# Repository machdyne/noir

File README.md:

# Noir Computer

Noir is an FPGA computer designed by Lone Dynamics Corporation.

This repo contains schematics, PCB layouts, pinouts, a 3D-printable case, example gateware and documentation.

Find more information on the [Noir product page](https://machdyne.com/product/noir-computer/).

## Dual-Core Bitstream

There is now a dual-core bitstream optimized for speed that significantly decreases boot time and adds a second RISC-V core.

In addition to updating to this bitstream (`images/v0/noir_dual.bit`), make sure you copy the `images/linux/noir_dual.dtb` file to the SD card and update `boot.json` to use `noir_dual.dtb`.

## Programming Noir

Noir has a JTAG interface and ships with a [DFU bootloader](https://github.com/machdyne/tinydfu-bootloader) that allows the included flash [MMOD](https://machdyne.com/product/mmod) to be programmed over the USB-C port.

### DFU

The DFU bootloader is available for 5 seconds after power-on, issuing a DFU command during this period will stop the boot process until the DFU device is detached. If no command is received the boot process will continue and the user gateware will be loaded.

Install [dfu-util](http://dfu-util.sourceforge.net) (Debian/Ubuntu):

```
$ sudo apt install dfu-util
```

Update the user gateware on the flash MMOD:

```
$ sudo dfu-util -a 0 -D image.bit
```

Detach the DFU device and continue the boot process:

```
$ sudo dfu-util -a 0 -e
```

It is possible to update the bootloader itself using DFU but you shouldn't attempt this unless you have a JTAG programmer (or another method to program the MMOD) available, in case you need to restore the bootloader.

### JTAG

These examples assume you're using a "USB Blaster" JTAG cable, see the header pinout below. You will need to have [openFPGALoader](https://github.com/trabucayre/openFPGALoader) installed.

Program the configuration SRAM:

```
openFPGALoader -c usb-blaster image.bit
```

Program the flash MMOD:

```
openFPGALoader -f -c usb-blaster images/bootloader/tinydfu_noir.bit
```

## Blinky 

Building the blinky example requires [Yosys](https://github.com/YosysHQ/yosys), [nextpnr-ecp5](https://github.com/YosysHQ/nextpnr) and [Project Trellis](https://github.com/YosysHQ/prjtrellis).

Assuming they are installed, you can simply type `make` to build the gateware, which will be written to output/blinky.bin. You can then use [openFPGALoader](https://github.com/trabucayre/openFPGALoader) or dfu-util to write the gateware to the device.

## Linux

See the [Kakao Linux](https://github.com/machdyne/kakao) repo for the latest instructions.

### Prebuilt Images

Copy the files from the `images/linux` directory to the root directory of a FAT-formatted MicroSD card.

Noir ships with LiteX gateware on the user gateware section of the MMOD that is compatible with these images. After several seconds the Linux penguin should appear on the screen (HDMI) followed by a login prompt.

### Building Linux

Please follow the setup instructions in the [linux-on-litex-vexriscv](https://github.com/litex-hub/linux-on-litex-vexriscv) repo and then:

1. Build the Linux-capable gateware:

```
$ cd linux-on-litex-vexriscv
$ ./make.py --board noir --uart-baudrate 115200 --build

$ ls build/noir
```

2. Write the gateware to the MMOD using USB DFU:

```
$ sudo dfu-util -a 0 -D build/noir/gateware/noir.bit
```

3. Copy the device tree binary `build/noir/noir.dtb` to a FAT-formatted MicroSD card.

4. Build the Linux kernel and root filesystem:

```
$ cd ..
$ git clone http://github.com/buildroot/buildroot
$ cd buildroot
$ make BR2_EXTERNAL=../linux-on-litex-vexriscv/buildroot/ litex_vexriscv_usbhost_defconfig
```

Optionally customize the kernel and buildroot packages:

```
$ make menuconfig
```

Build the kernel and rootfs:

```
$ make
$ ls output/images
```

5. Copy the `Image` and `rootfs.cpio` files from output/images to the MicroSD card.

6. Copy the OpenSBI binary (included in this repo as `noir/images/linux/opensbi.bin`) to the MicroSD card. Alternatively, you can build this binary by following [these instructions](https://github.com/litex-hub/linux-on-litex-vexriscv#-generating-the-opensbi-binary-optional).

7. Copy `noir/images/linux/boot.json` to the MicroSD card.

8. Power-cycle Noir. After Linux has finished booting you should see a login prompt on the HDMI display.

## LiteX

### Installing LiteX

If you haven't yet installed LiteX please see the [LiteX quick start guide](https://github.com/enjoy-digital/litex#quick-start-guide) for details on installing LiteX.

### Building Custom Gateware

Build the LiteX gateware:

```
$ cd litex-boards/litex_boards/targets
$ ./machdyne_noir.py --cpu-type=vexriscv --cpu-variant=lite --sys-clk-freq 40000000 --uart-baudrate 1000000 --uart-name serial --build
```

Program the LiteX gateware to SRAM over JTAG:

```
$ ./machdyne_noir.py --cable usb-blaster --load
```

Or program the LiteX gateware to flash over DFU:

```
$ sudo dfu-util -a 0 -D build/machdyne_noir/gateware/machdyne_noir.bit
```

## JTAG Header

The 3.3V JTAG header can be used to program the FPGA SRAM as well as the MMOD flash memory. It can also be used to provide power (5V) to the board.

```
1 2
3 4
5 6
```

| Pin | Signal |
| --- | ------ |
| 1 | TCK |
| 2 | TDI |
| 3 | TDO |
| 4 | TMS |
| 5 | 5V0 |
| 6 | GND |

## Resources

 * [fpga-dac audio player](https://github.com/machdyne/fpga-dac)

## Board Revisions

| Revision | Notes |
| -------- | ----- |
| V0 | Initial version |
| V1 | Work in progress; adds composite video DAC output to 3.5mm jack |

## License

The contents of this repo are released under the [Lone Dynamics Open License](LICENSE.md) with the following exceptions:

- The KiCad design files contain parts of the [kicad-pmod](https://github.com/mithro/kicad-pmod) library which is released under the [Apache License, Version 2.0](https://www.apache.org/licenses/LICENSE-2.0.html).

- The KiCad design files may contain symbols and footprints released under other licenses; please contact us if we've failed to give proper attribution.

Note: You can use these designs for commercial purposes but we ask that instead of producing exact clones, that you either replace our trademarks and logos with your own or add your own next to ours.

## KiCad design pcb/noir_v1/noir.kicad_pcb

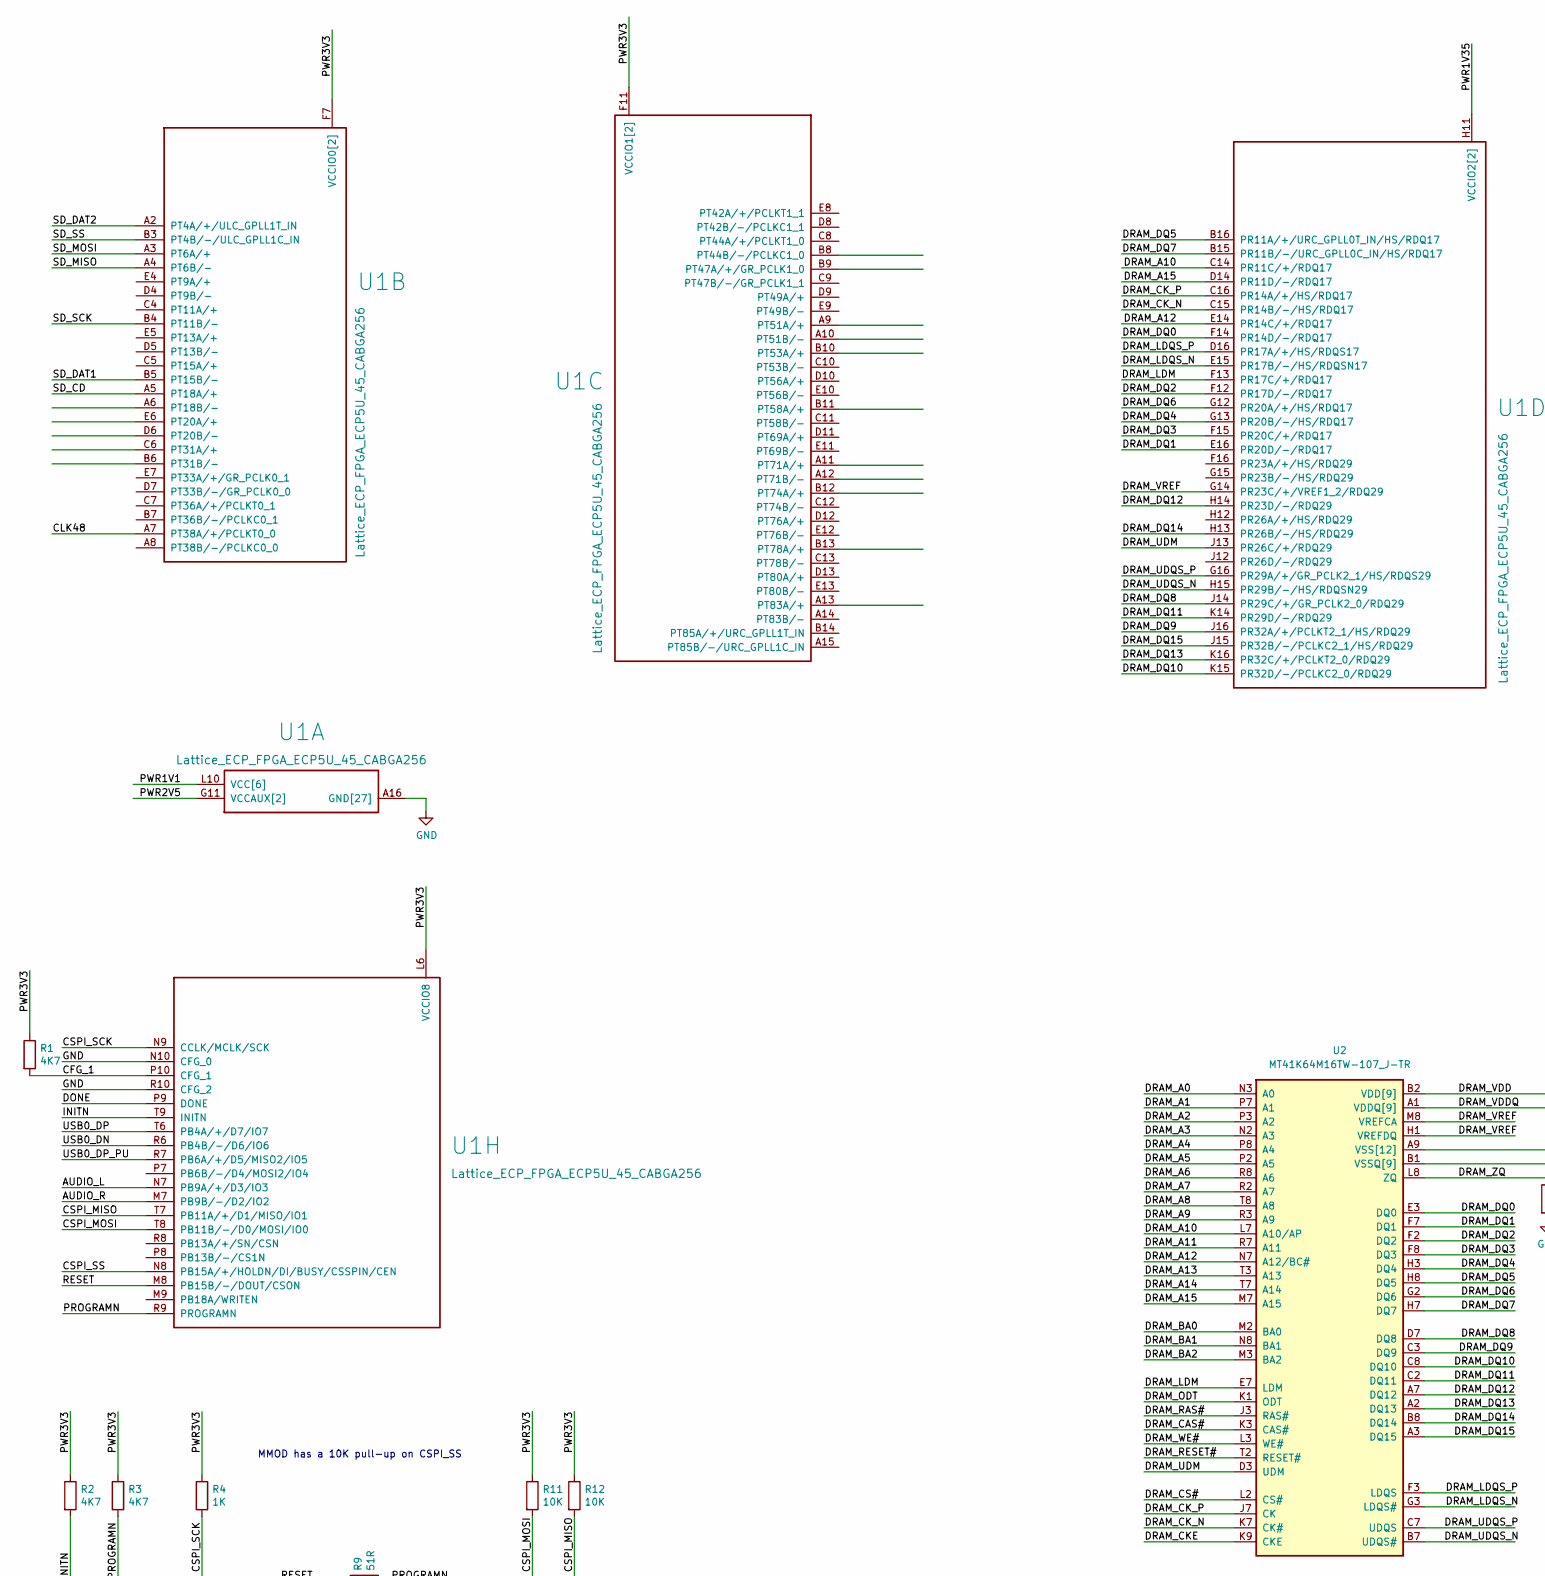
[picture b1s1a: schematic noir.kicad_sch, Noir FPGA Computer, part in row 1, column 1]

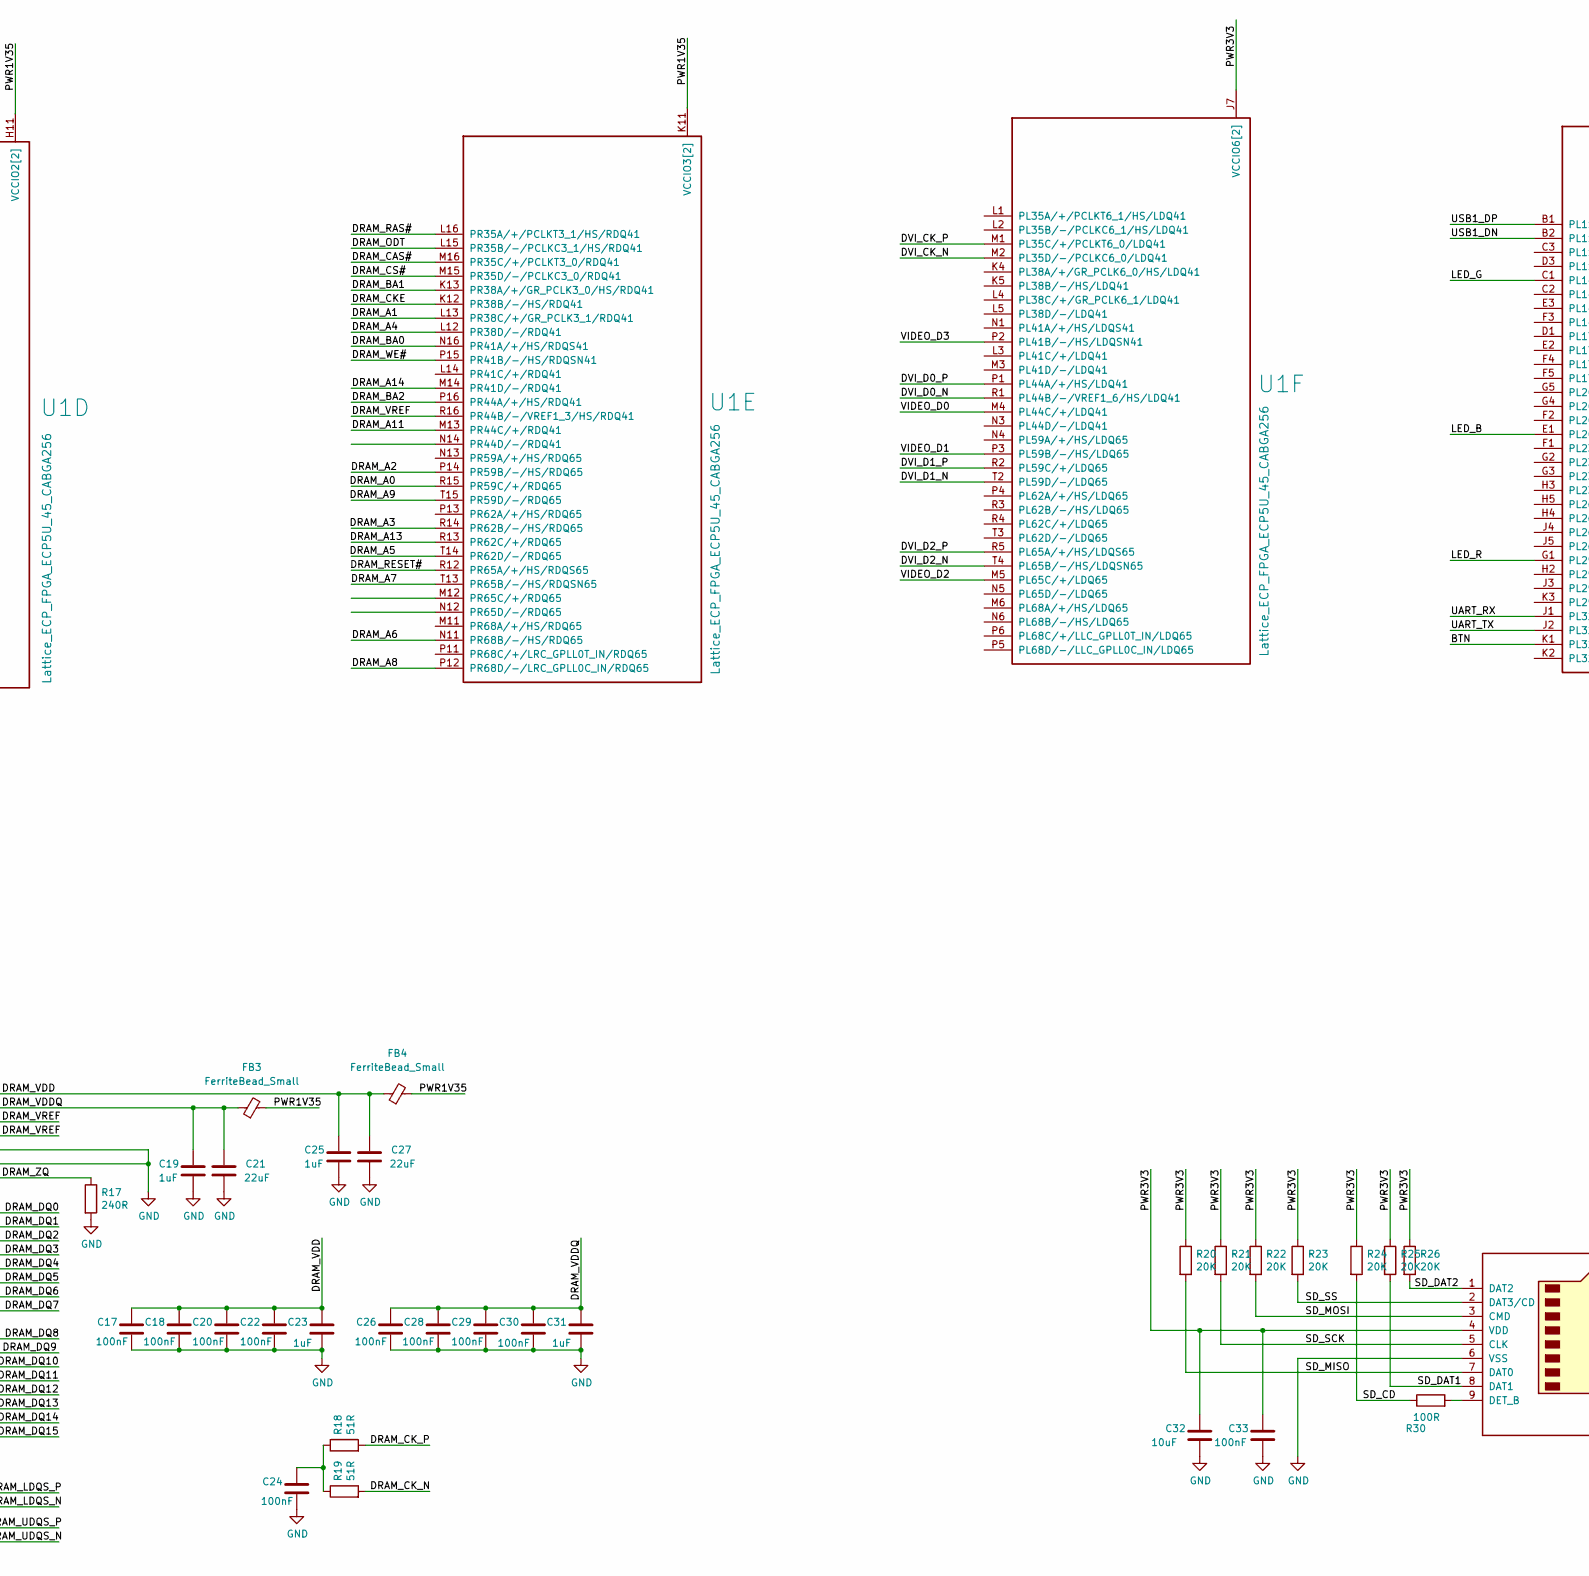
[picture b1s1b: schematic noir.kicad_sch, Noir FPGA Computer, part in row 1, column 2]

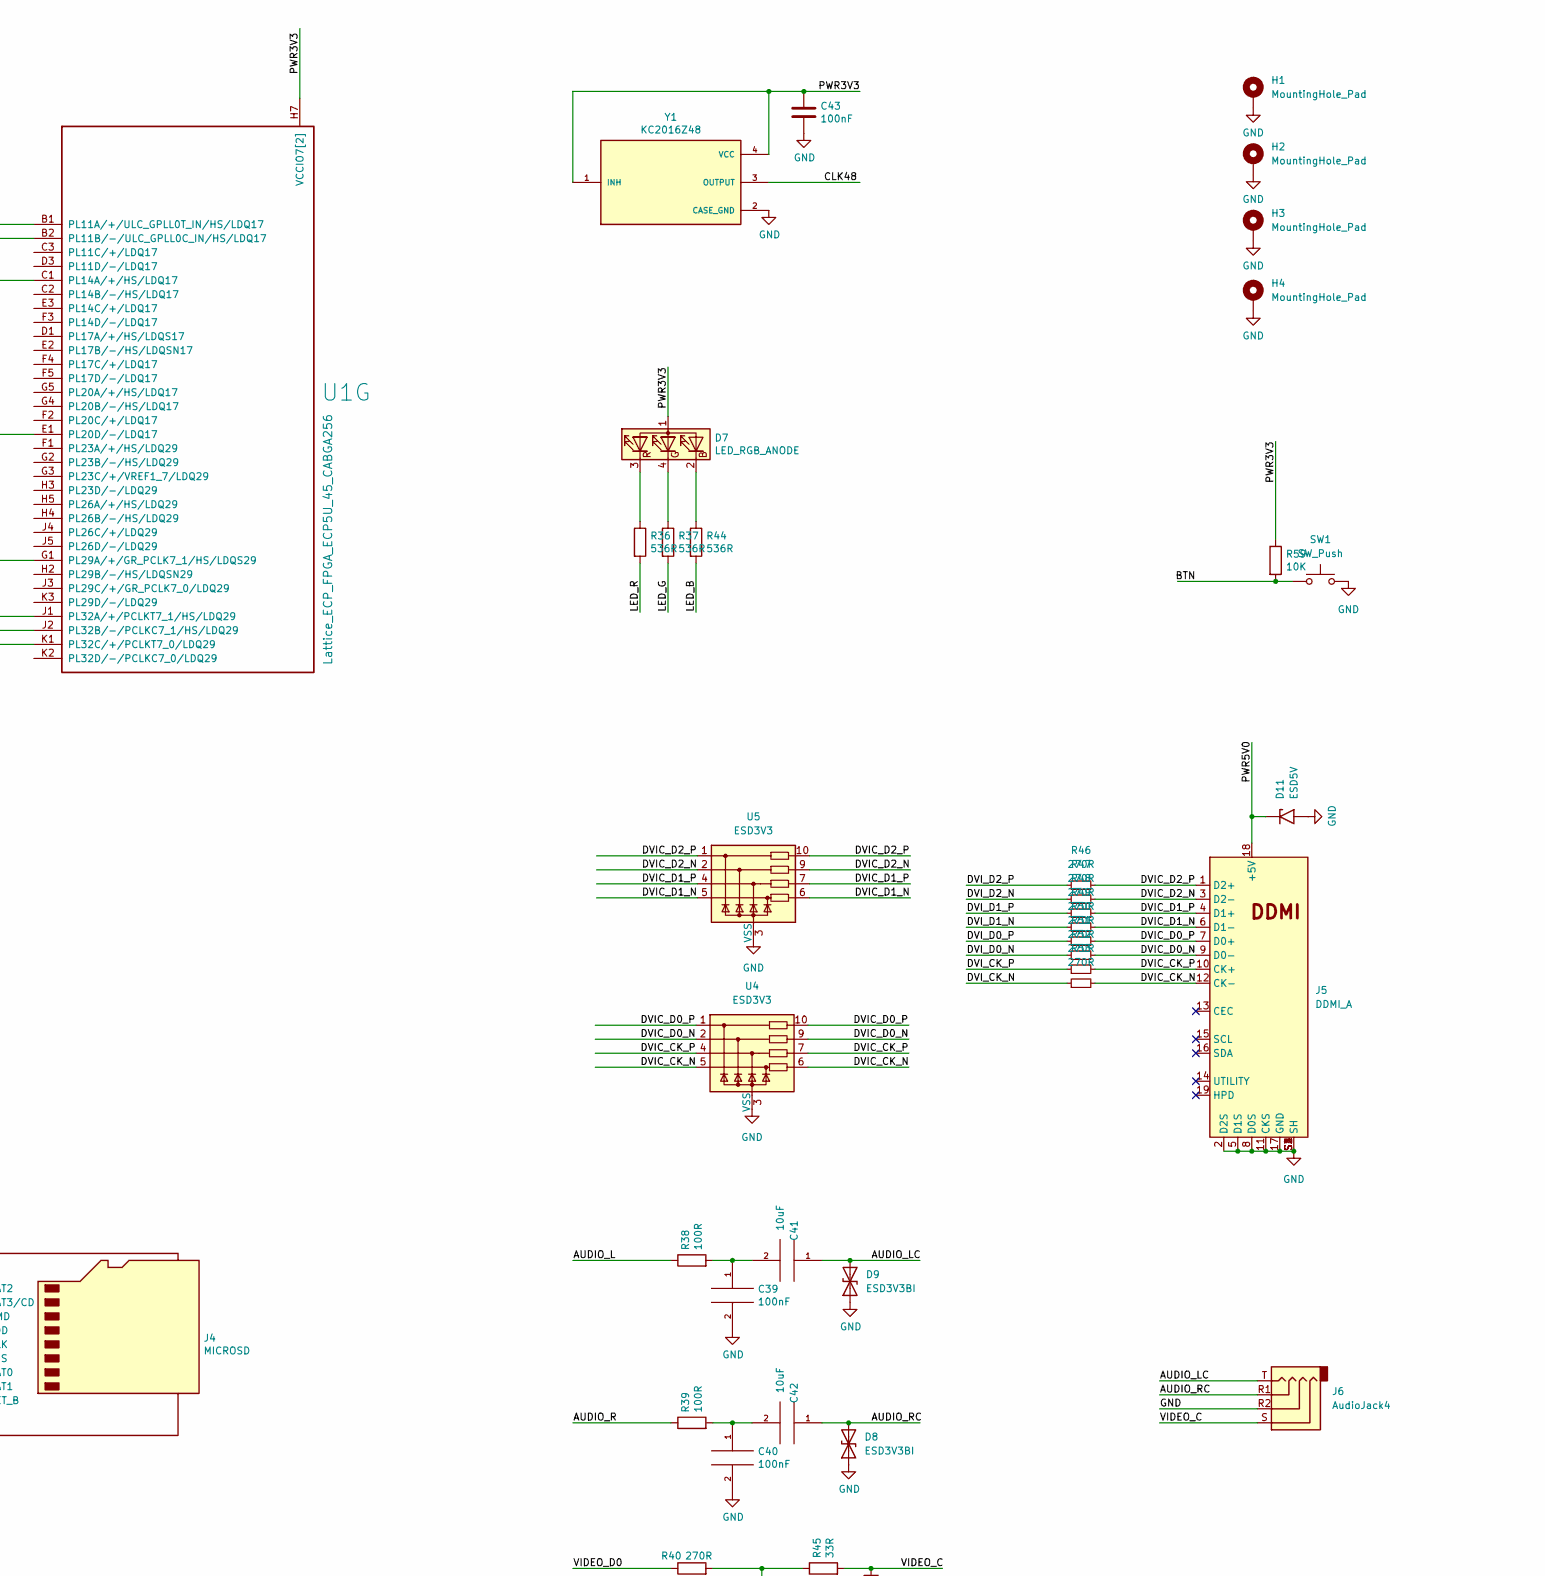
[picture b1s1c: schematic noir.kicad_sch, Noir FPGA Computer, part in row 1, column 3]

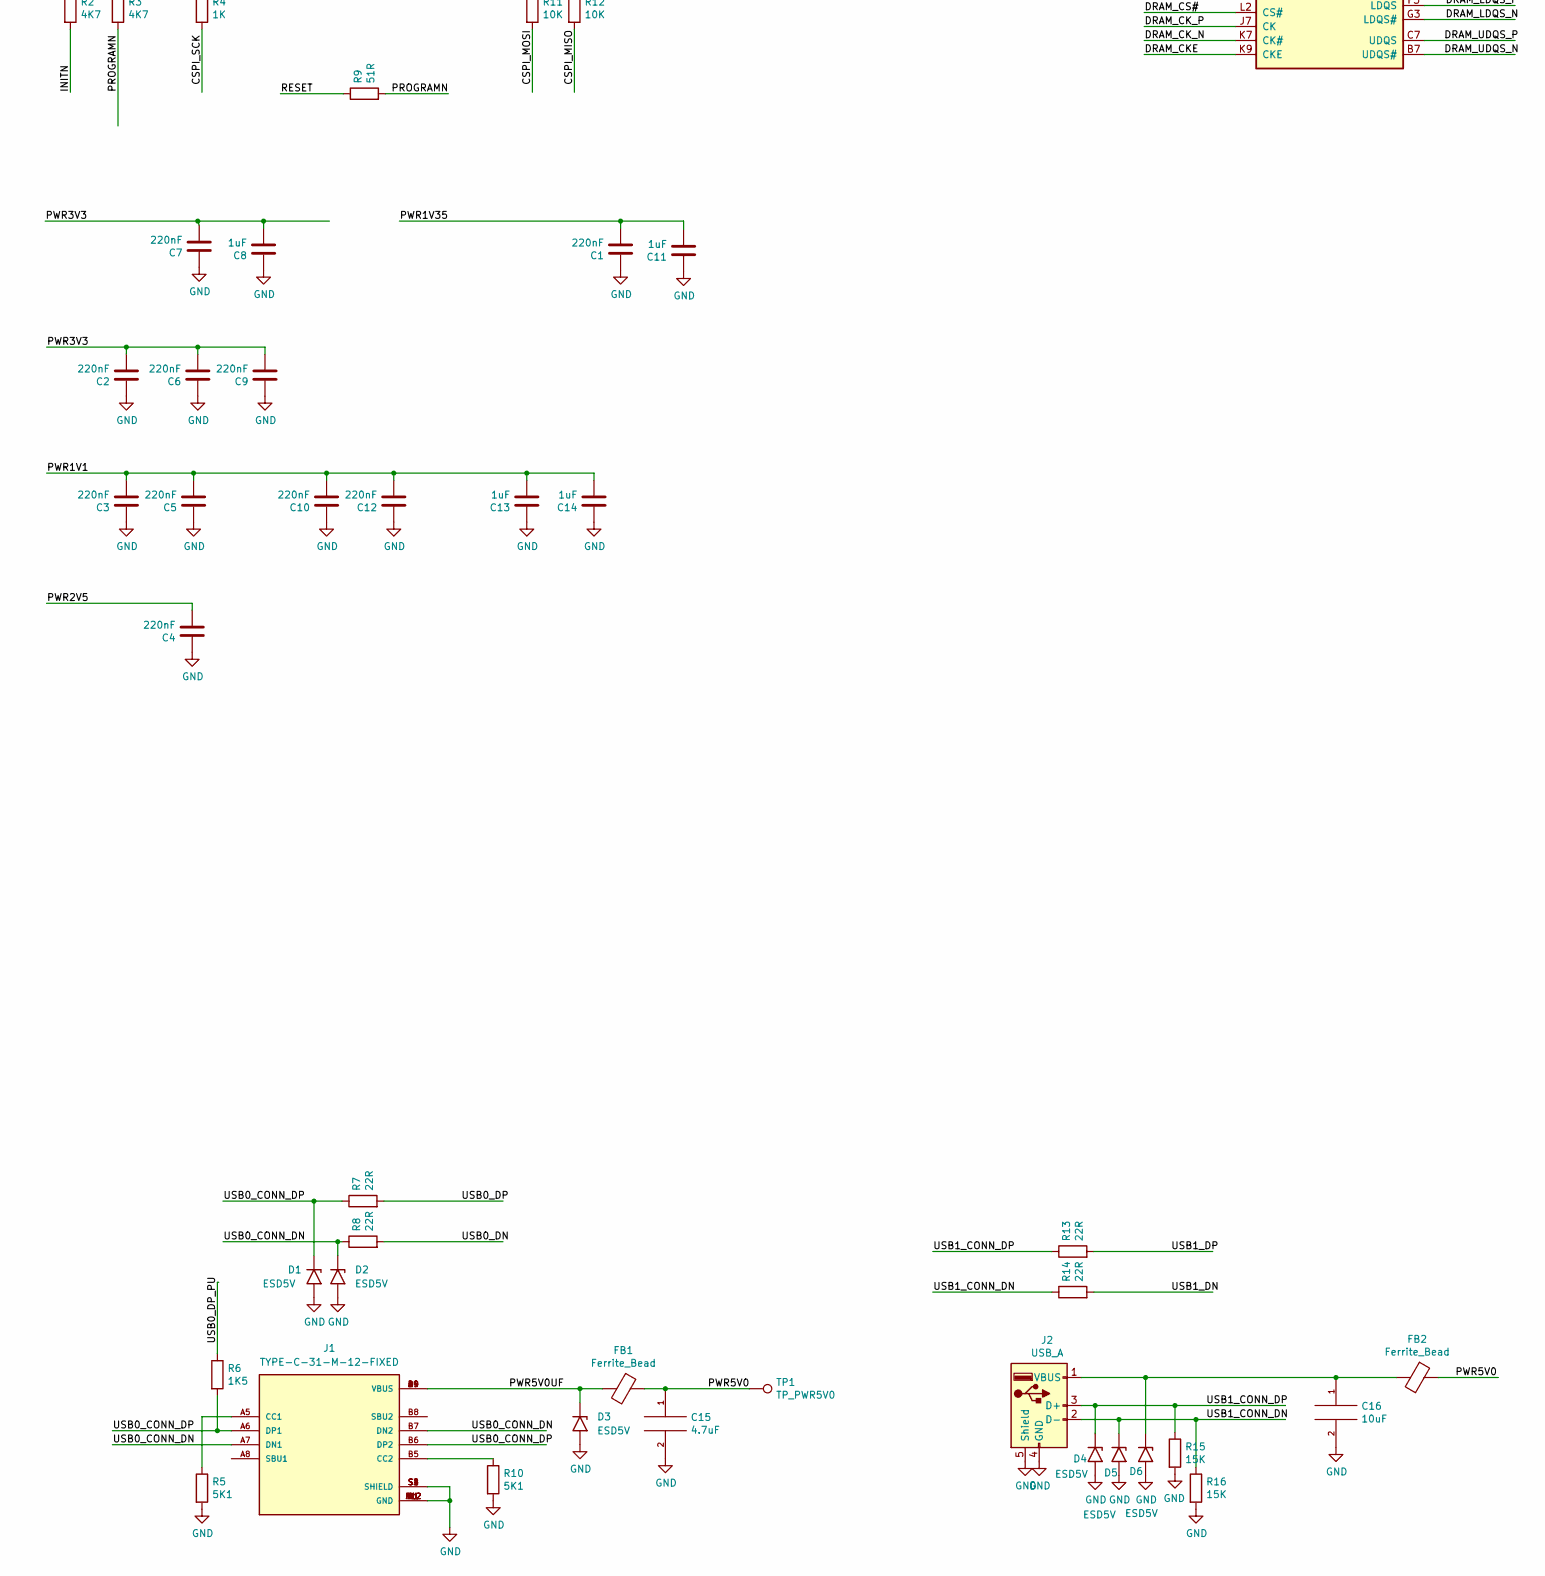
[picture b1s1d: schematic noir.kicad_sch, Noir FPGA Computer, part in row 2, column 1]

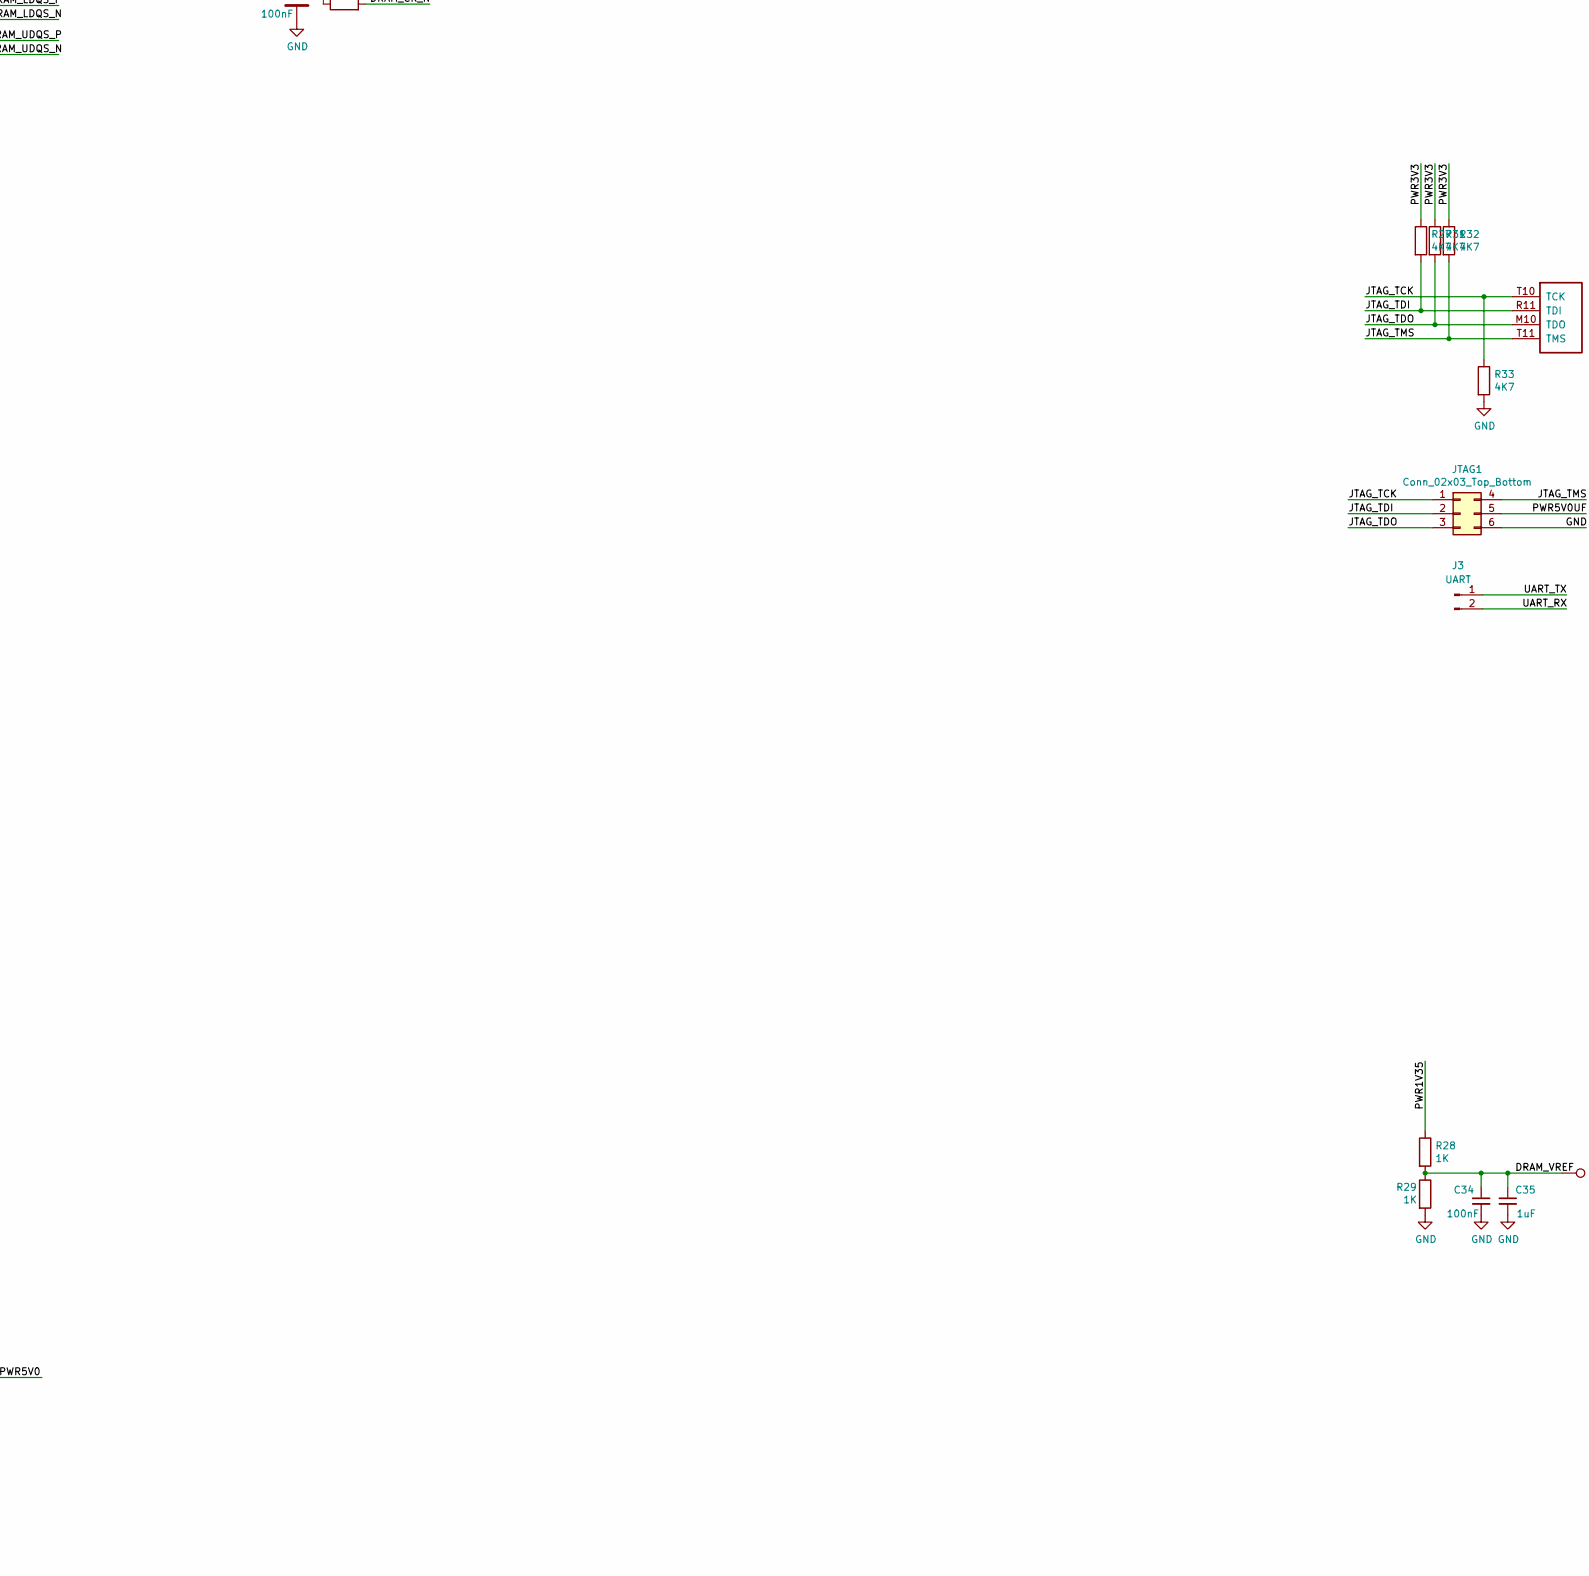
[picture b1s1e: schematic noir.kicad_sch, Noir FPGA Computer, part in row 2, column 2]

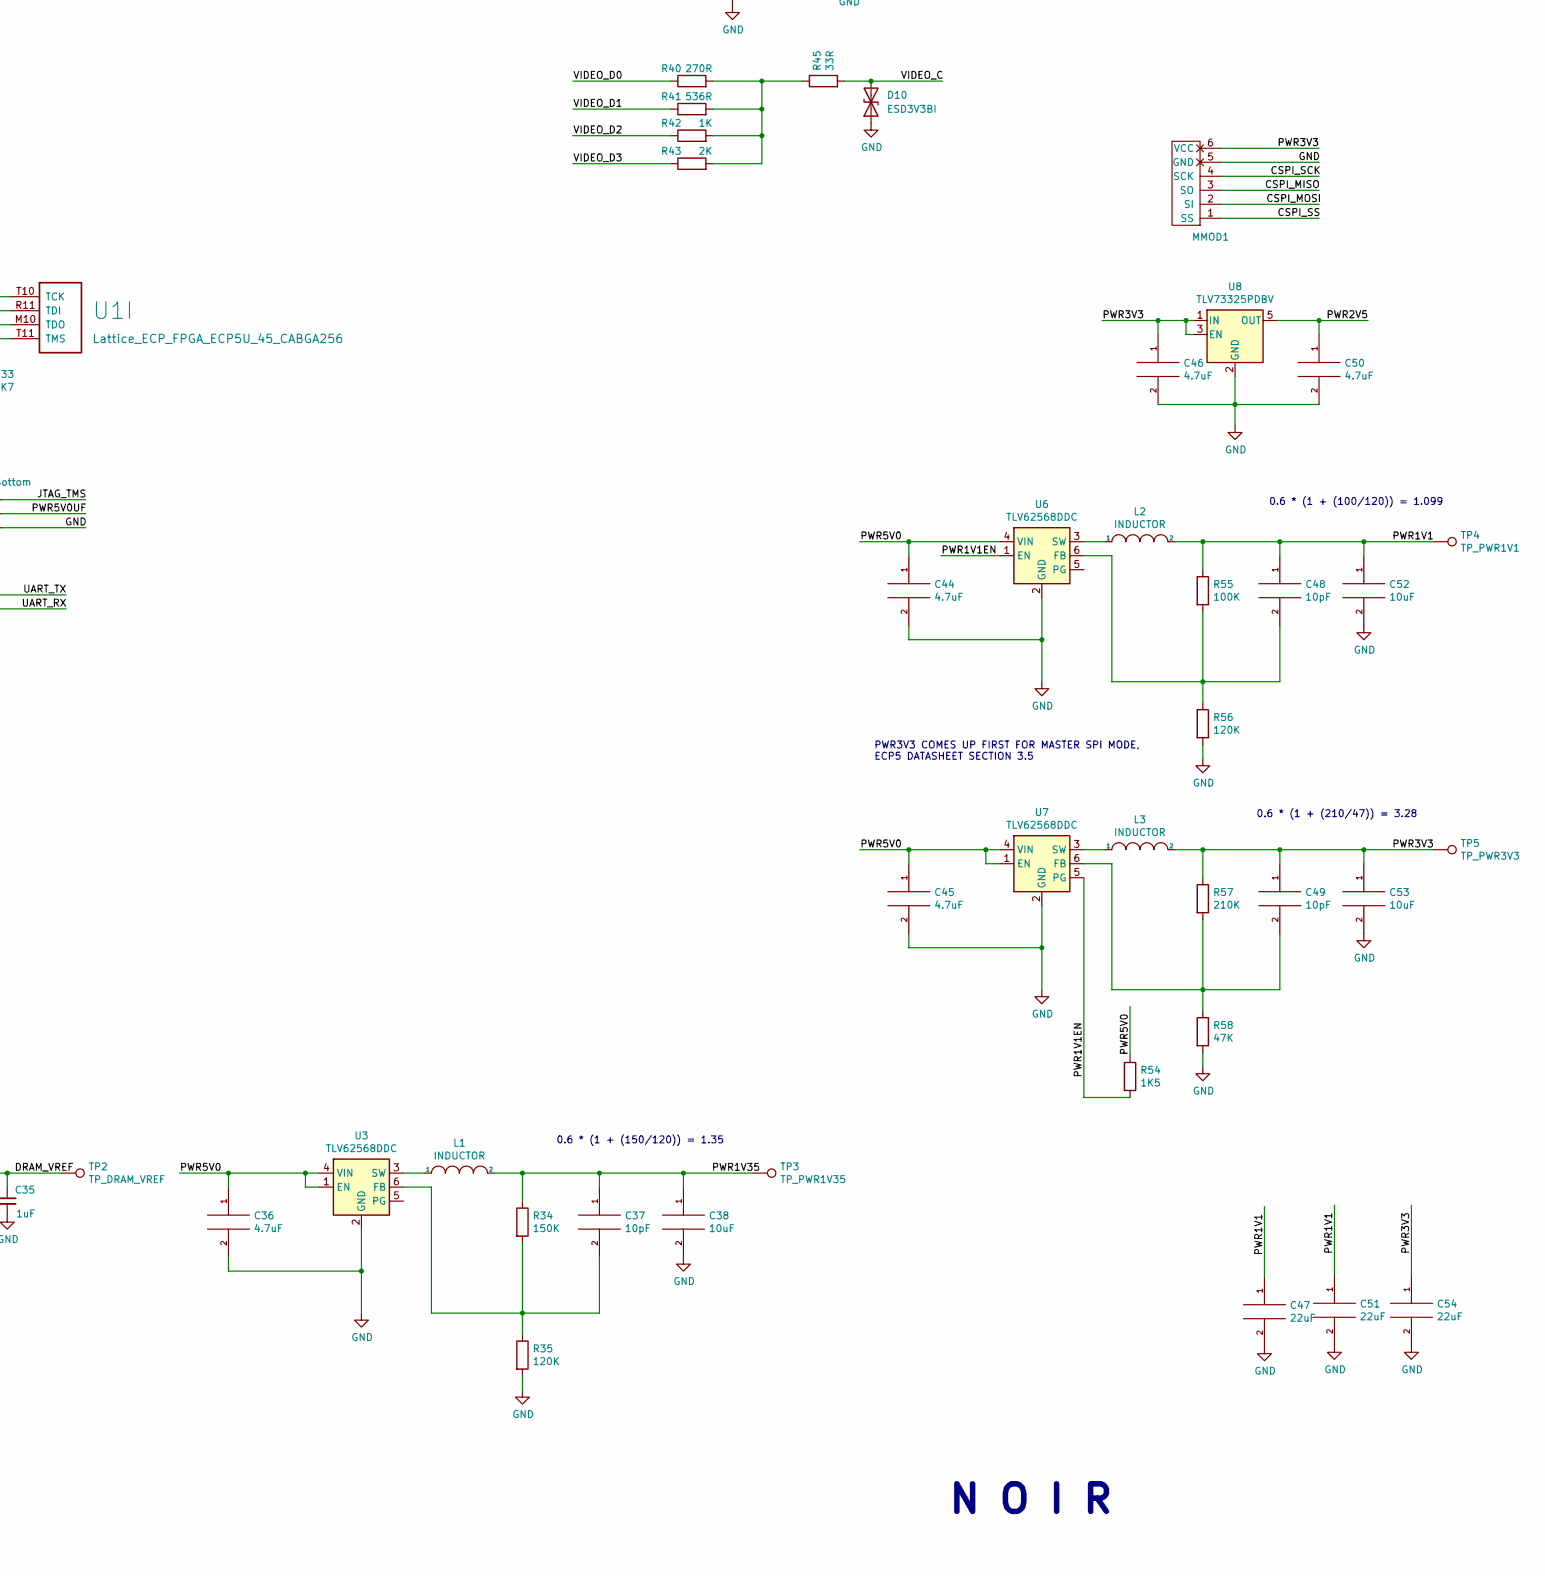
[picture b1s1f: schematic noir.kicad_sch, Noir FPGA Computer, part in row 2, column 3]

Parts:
C1, C2, C3, C4, C5, C6, C7, C9, C10, C12: 220nF; C_0603_1608Metric
C8, C11, C13, C14, C35: 1uF; C_0603_1608Metric
C15, C36, C44, C45, C46, C50: 4.7uF; C_0603_1608Metric
C16, C38, C41, C42, C52, C53: 10uF; C_0603_1608Metric
C17, C18, C20, C22, C26, C28, C29, C30: 100nF; C_0402_1005Metric
C19, C23, C25, C31: 1uF; C_0402_1005Metric
C21, C27: 22uF; R_0603_1608Metric
C24, C33, C43: 100nF; R_0603_1608Metric
C32: 10uF; R_0603_1608Metric
C34, C39, C40: 100nF; C_0603_1608Metric
C37, C48, C49: 10pF; C_0603_1608Metric
C47, C51, C54: 22uF; C_0603_1608Metric
D1, D2, D3, D4, D5, D6, D11: ESD5V; D_SOD-523
D7: LED_RGB_ANODE; LED_RGB_0606_CHANZON
D8, D9, D10: ESD3V3BI; D_SOD-523
FB1, FB2: Ferrite_Bead; R_0603_1608Metric
FB3, FB4: FerriteBead_Small; R_0603_1608Metric
H1, H2, H3, H4: MountingHole_Pad; MountingHole_3.2mm_M3_Pad
J1: TYPE-C-31-M-12-FIXED; USB_C_Receptacle_HRO_TYPE-C-31-M-12-BIG-PADS; PARTREV A
J2: USB_A; USB_A_Stewart_SS-52100-001_Horizontal
J3: UART; PinHeader_1x02_P2.54mm_Vertical
J4: MICROSD; SDCARD
J5: DDMI_A; HDMI_TE_1827059-3-FIXED
J6: AudioJack4; Jack_3.5mm_PJ320D_Horizontal
JTAG1: Conn_02x03_Top_Bottom; PinHeader_2x03_P2.54mm_Vertical
L1, L2, L3: INDUCTOR; L_0805_2012Metric
MMOD1: PMOD-Device-x1-Type-2-SPI; MMOD_Host_Socket
R1, R2, R3, R27, R31, R32, R33: 4K7; R_0603_1608Metric
R4, R28, R29, R42: 1K; R_0603_1608Metric
R5, R10: 5K1; R_0603_1608Metric
R6, R54: 1K5; R_0603_1608Metric
R7, R8, R13, R14: 22R; R_0603_1608Metric
R9, R18, R19: 51R; R_0603_1608Metric
R11, R12, R59: 10K; R_0603_1608Metric
R15, R16: 15K; R_0603_1608Metric
R17: 240R; R_0603_1608Metric
R20, R21, R22, R23, R24, R25, R26: 20K; R_0603_1608Metric
R30, R38, R39: 100R; R_0603_1608Metric
R34: 150K; R_0603_1608Metric
R35, R56: 120K; R_0603_1608Metric
R36, R37, R41, R44: 536R; R_0603_1608Metric
R40: 270R; R_0603_1608Metric
R43: 2K; R_0603_1608Metric
R45: 33R; R_0603_1608Metric
R46, R47, R48, R49, R50, R51, R52, R53: 270R; R_0402_1005Metric
R55: 100K; R_0603_1608Metric
R57: 210K; R_0603_1608Metric
R58: 47K; R_0603_1608Metric
SW1: SW_Push; Button_2P_3x4mm
TP1: TP_PWR5V0; TestPoint_THTPad_D1.0mm_Drill0.5mm
TP2: TP_DRAM_VREF; TestPoint_THTPad_D1.0mm_Drill0.5mm
TP3: TP_PWR1V35; TestPoint_THTPad_D1.0mm_Drill0.5mm
TP4: TP_PWR1V1; TestPoint_THTPad_D1.0mm_Drill0.5mm
TP5: TP_PWR3V3; TestPoint_THTPad_D1.0mm_Drill0.5mm
U1: Lattice_ECP_FPGA_ECP5U_45_CABGA256; BGA-256_14.0x14.0mm_Layout16x16_P0.8mm_Ball0.45mm_Pad0.32mm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
U2: MT41K64M16TW-107_J-TR; BGA-96_9.0x13.0mm_Layout2x3x16_P0.8mm
U3, U6, U7: TLV62568DDC; SOT-23-6
U4, U5: ESD3V3; Diodes_UDFN-10_1.0x2.5mm_P0.5mm
U8: TLV73325PDBV; SOT-23-5
Y1: KC2016Z48; OSC_KC2016Z13.5600C1KX00; PARTREV November 2020

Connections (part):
/AUDIO_L: R38.1, U1.N7 (PB9A/+/D3/IO3)
/AUDIO_LC: C41.1, D9.2 (A2), J6.T
/AUDIO_R: R39.1, U1.M7 (PB9B/-/D2/IO2)
/AUDIO_RC: C42.1, D8.2 (A2), J6.R1
/BTN: R59.2, SW1.1, U1.K1 (PL32C/+/PCLKT7_0/LDQ29)
/CFG_1: R1.2, U1.P10 (CFG_1)
/CLK48: U1.A7 (PT38A/+/PCLKT0_0), Y1.3 (OUTPUT)
/CSPI_MISO: MMOD1.3 (SO), R12.2, U1.T7 (PB11A/+/D1/MISO/IO1)
/CSPI_MOSI: MMOD1.2 (SI), R11.2, U1.T8 (PB11B/-/D0/MOSI/IO0)
/CSPI_SCK: MMOD1.4 (SCK), R4.2, U1.N9 (CCLK/MCLK/SCK)
/CSPI_SS: MMOD1.1 (SS), U1.N8 (PB15A/+/HOLDN/DI/BUSY/CSSPIN/CEN)
/DONE: U1.P9 (DONE)
/DRAM_A0: U1.R15 (PR59C/+/RDQ65), U2.N3 (A0)
/DRAM_A1: U1.L13 (PR38C/+/GR_PCLK3_1/RDQ41), U2.P7 (A1)
/DRAM_A2: U1.P14 (PR59B/-/HS/RDQ65), U2.P3 (A2)
/DRAM_A3: U1.R14 (PR62B/-/HS/RDQ65), U2.N2 (A3)
/DRAM_A4: U1.L12 (PR38D/-/RDQ41), U2.P8 (A4)
/DRAM_A5: U1.T14 (PR62D/-/RDQ65), U2.P2 (A5)
/DRAM_A6: U1.N11 (PR68B/-/HS/RDQ65), U2.R8 (A6)
/DRAM_A7: U1.T13 (PR65B/-/HS/RDQSN65), U2.R2 (A7)
/DRAM_A8: U1.P12 (PR68D/-/LRC_GPLL0C_IN/RDQ65), U2.T8 (A8)
/DRAM_A9: U1.T15 (PR59D/-/RDQ65), U2.R3 (A9)
/DRAM_A10: U1.C14 (PR11C/+/RDQ17), U2.L7 (A10/AP)
/DRAM_A11: U1.M13 (PR44C/+/RDQ41), U2.R7 (A11)
/DRAM_A12: U1.E14 (PR14C/+/RDQ17), U2.N7 (A12/BC#)
/DRAM_A13: U1.R13 (PR62C/+/RDQ65), U2.T3 (A13)
/DRAM_A14: U1.M14 (PR41D/-/RDQ41), U2.T7 (A14)
/DRAM_A15: U1.D14 (PR11D/-/RDQ17), U2.M7 (A15)
/DRAM_BA0: U1.N16 (PR41A/+/HS/RDQS41), U2.M2 (BA0)
/DRAM_BA1: U1.K13 (PR38A/+/GR_PCLK3_0/HS/RDQ41), U2.N8 (BA1)
/DRAM_BA2: U1.P16 (PR44A/+/HS/RDQ41), U2.M3 (BA2)
/DRAM_CAS#: U1.M16 (PR35C/+/PCLKT3_0/RDQ41), U2.K3 (CAS#)
/DRAM_CKE: U1.K12 (PR38B/-/HS/RDQ41), U2.K9 (CKE)
/DRAM_CK_N: R19.2, U1.C15 (PR14B/-/HS/RDQ17), U2.K7 (CK#)
/DRAM_CK_P: R18.2, U1.C16 (PR14A/+/HS/RDQ17), U2.J7 (CK)
/DRAM_CS#: U1.M15 (PR35D/-/PCLKC3_0/RDQ41), U2.L2 (CS#)
/DRAM_DQ0: U1.F14 (PR14D/-/RDQ17), U2.E3 (DQ0)
/DRAM_DQ1: U1.E16 (PR20D/-/RDQ17), U2.F7 (DQ1)
/DRAM_DQ2: U1.F12 (PR17D/-/RDQ17), U2.F2 (DQ2)
/DRAM_DQ3: U1.F15 (PR20C/+/RDQ17), U2.F8 (DQ3)
/DRAM_DQ4: U1.G13 (PR20B/-/HS/RDQ17), U2.H3 (DQ4)
/DRAM_DQ5: U1.B16 (PR11A/+/URC_GPLL0T_IN/HS/RDQ17), U2.H8 (DQ5)
/DRAM_DQ6: U1.G12 (PR20A/+/HS/RDQ17), U2.G2 (DQ6)
/DRAM_DQ7: U1.B15 (PR11B/-/URC_GPLL0C_IN/HS/RDQ17), U2.H7 (DQ7)
/DRAM_DQ8: U1.J14 (PR29C/+/GR_PCLK2_0/RDQ29), U2.D7 (DQ8)
/DRAM_DQ9: U1.J16 (PR32A/+/PCLKT2_1/HS/RDQ29), U2.C3 (DQ9)
/DRAM_DQ10: U1.K15 (PR32D/-/PCLKC2_0/RDQ29), U2.C8 (DQ10)
/DRAM_DQ11: U1.K14 (PR29D/-/RDQ29), U2.C2 (DQ11)
/DRAM_DQ12: U1.H14 (PR23D/-/RDQ29), U2.A7 (DQ12)
/DRAM_DQ13: U1.K16 (PR32C/+/PCLKT2_0/RDQ29), U2.A2 (DQ13)
/DRAM_DQ14: U1.H13 (PR26B/-/HS/RDQ29), U2.B8 (DQ14)
/DRAM_DQ15: U1.J15 (PR32B/-/PCLKC2_1/HS/RDQ29), U2.A3 (DQ15)
/DRAM_LDM: U1.F13 (PR17C/+/RDQ17), U2.E7 (LDM)
/DRAM_LDQS_N: U1.E15 (PR17B/-/HS/RDQSN17), U2.G3 (LDQS#)
/DRAM_LDQS_P: U1.D16 (PR17A/+/HS/RDQS17), U2.F3 (LDQS)
/DRAM_ODT: U1.L15 (PR35B/-/PCLKC3_1/HS/RDQ41), U2.K1 (ODT)
/DRAM_RAS#: U1.L16 (PR35A/+/PCLKT3_1/HS/RDQ41), U2.J3 (RAS#)
/DRAM_RESET#: U1.R12 (PR65A/+/HS/RDQS65), U2.T2 (RESET#)
/DRAM_UDM: U1.J13 (PR26C/+/RDQ29), U2.D3 (UDM)
/DRAM_UDQS_N: U1.H15 (PR29B/-/HS/RDQSN29), U2.B7 (UDQS#)
/DRAM_UDQS_P: U1.G16 (PR29A/+/GR_PCLK2_1/HS/RDQS29), U2.C7 (UDQS)
/DRAM_VDD: C17.1, C18.1, C20.1, C22.1, C23.1, C25.1, C27.1, FB4.1, U2.B2 (VDD[9]), U2.D9 (VDD), U2.G7 (VDD), U2.K2 (VDD), U2.K8 (VDD), U2.N1 (VDD), U2.N9 (VDD), U2.R1 (VDD), U2.R9 (VDD)
/DRAM_VDDQ: C19.1, C21.1, C26.1, C28.1, C29.1, C30.1, C31.1, FB3.1, U2.A1 (VDDQ[9]), U2.A8 (VDDQ), U2.C1 (VDDQ), U2.C9 (VDDQ), U2.D2 (VDDQ), U2.E9 (VDDQ), U2.F1 (VDDQ), U2.H2 (VDDQ), U2.H9 (VDDQ)
/DRAM_VREF: C34.1, C35.1, R28.2, R29.1, TP2.1, U1.G14 (PR23C/+/VREF1_2/RDQ29), U1.R16 (PR44B/-/VREF1_3/HS/RDQ41), U2.H1 (VREFDQ), U2.M8 (VREFCA)
/DRAM_WE#: U1.P15 (PR41B/-/HS/RDQSN41), U2.L3 (WE#)
/DRAM_ZQ: R17.1, U2.L8 (ZQ)
/DVIC_CK_N: J5.12 (CK-), R53.2, U4.5, U4.6
/DVIC_CK_P: J5.10 (CK+), R52.2, U4.4, U4.7
/DVIC_D0_N: J5.9 (D0-), R51.2, U4.2, U4.9
/DVIC_D0_P: J5.7 (D0+), R50.2, U4.1, U4.10
/DVIC_D1_N: J5.6 (D1-), R49.2, U5.5, U5.6
/DVIC_D1_P: J5.4 (D1+), R48.2, U5.4, U5.7
/DVIC_D2_N: J5.3 (D2-), R47.2, U5.2, U5.9
/DVIC_D2_P: J5.1 (D2+), R46.2, U5.1, U5.10
/DVI_CK_N: R53.1, U1.M2 (PL35D/-/PCLKC6_0/LDQ41)
/DVI_CK_P: R52.1, U1.M1 (PL35C/+/PCLKT6_0/LDQ41)
/DVI_D0_N: R51.1, U1.R1 (PL44B/-/VREF1_6/HS/LDQ41)
/DVI_D0_P: R50.1, U1.P1 (PL44A/+/HS/LDQ41)
/DVI_D1_N: R49.1, U1.T2 (PL59D/-/LDQ65)
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
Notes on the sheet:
N O I R
PWR3V3 COMES UP FIRST FOR MASTER SPI MODE, ECP5 DATASHEET SECTION 3.5
0.6 * (1 + (210/47)) = 3.28
MMOD has a 10K pull-up on CSPI_SS
0.6 * (1 + (100/120)) = 1.099
0.6 * (1 + (150/120)) = 1.35

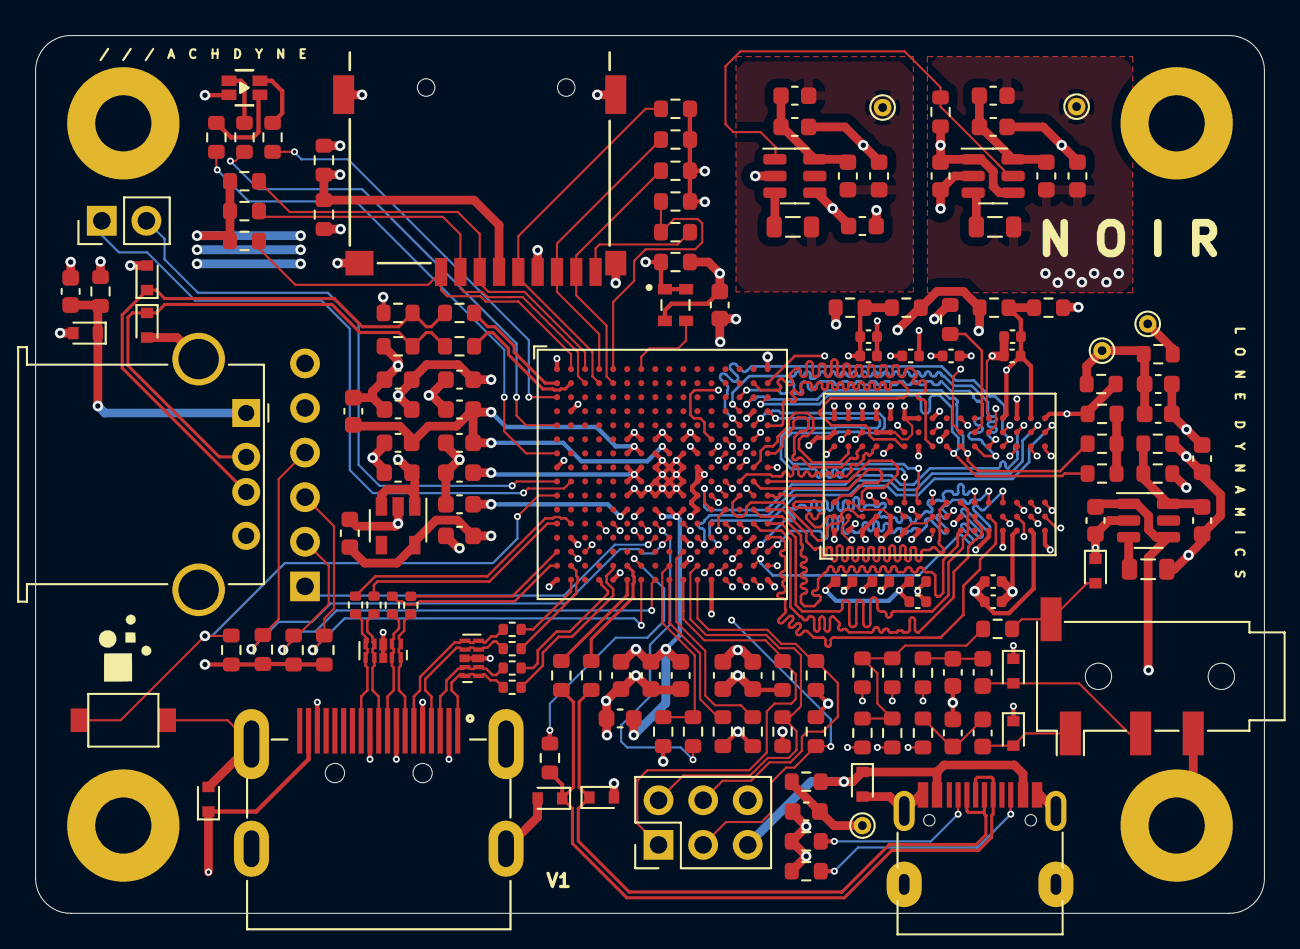
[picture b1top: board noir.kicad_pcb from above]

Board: 6 copper layers, 70.0 x 50.0 mm, 158 parts (1 on the bottom side), 139 nets.

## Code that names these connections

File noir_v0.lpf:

BLOCK RESETPATHS;
BLOCK ASYNCPATHS;

# CLOCK
LOCATE COMP "CLK_48" SITE "A7";
IOBUF  PORT "CLK_48" PULLMODE=NONE IO_TYPE=LVCMOS33;
FREQUENCY PORT "CLK_48" 48 MHZ;

# JTAG and SPI FLASH voltage 3.3V and options to boot from SPI flash
# write to FLASH possible any time from JTAG:
SYSCONFIG CONFIG_IOVOLTAGE=3.3 COMPRESS_CONFIG=ON MCCLK_FREQ=2.4 MASTER_SPI_PORT=ENABLE SLAVE_SPI_PORT=DISABLE SLAVE_PARALLEL_PORT=DISABLE CONFIG_MODE=SPI_SERIAL;
#SYSCONFIG CONFIG_IOVOLTAGE=3.3 COMPRESS_CONFIG=ON MCCLK_FREQ=62 MASTER_SPI_PORT=ENABLE SLAVE_SPI_PORT=DISABLE SLAVE_PARALLEL_PORT=DISABLE;

# write to FLASH possible from user bitstream:
#SYSCONFIG CONFIG_IOVOLTAGE=3.3 COMPRESS_CONFIG=ON MCCLK_FREQ=62 MASTER_SPI_PORT=DISABLE SLAVE_SPI_PORT=DISABLE SLAVE_PARALLEL_PORT=DISABLE;

LOCATE COMP "LED_R" SITE "G1";
IOBUF  PORT "LED_R" PULLMODE=NONE IO_TYPE=LVCMOS33 DRIVE=4;

LOCATE COMP "LED_G" SITE "C1";
IOBUF  PORT "LED_G" PULLMODE=NONE IO_TYPE=LVCMOS33 DRIVE=4;

LOCATE COMP "LED_B" SITE "E1";
IOBUF  PORT "LED_B" PULLMODE=NONE IO_TYPE=LVCMOS33 DRIVE=4;

LOCATE COMP "USBH_DP" SITE "B1";
IOBUF  PORT "USBH_DP" PULLMODE=NONE IO_TYPE=LVCMOS33 DRIVE=4;

LOCATE COMP "USBH_DN" SITE "B2";
IOBUF  PORT "USBH_DN" PULLMODE=NONE IO_TYPE=LVCMOS33 DRIVE=4;

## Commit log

2022-12-30 add schematics
2022-12-30 add image
2022-12-30 fix makefile
2023-01-06 use sd mode instead of spi mode for sdcard
2023-02-05 update case
2023-05-07 add pcb
2023-07-19 add dual-core bitstream

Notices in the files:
pcb/noir_v1/noir.kicad_sch:
Copyright © 2022 Lone Dynamics Corporation
